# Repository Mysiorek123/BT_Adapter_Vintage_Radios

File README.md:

# Bluetooth Adapter for Vintage Radios

This project presents the design and implementation of a specialized Bluetooth adapter aimed at modernizing vintage radio receivers, such as the Polish Unitra Zodiak, while preserving their unique acoustic character. The hardware features a multi-stage power supply and signal isolation architecture, utilizing a bridge rectifier, high-capacity filtering, and a PS2561 optoisolator to eliminate hum and ground loops. 

# I/O Pinouts Description

- ~AC - AC Input Voltage (6,3V)
- J1 - Separated 1,2V DC Input
- J2 - Separated 1,2V Ground
- J3 - Bluetooth Power Supply (VCC)
- J4 - Bluetooth Ground (GND)

# Schematic Diagram

# PCB View

The physical implementation employs a double-sided PCB designed for a vertical "sandwich" stack configuration, ensuring full mechanical compatibility and efficient heat dissipation. 

# Components()
| Reference  | Footprint | Qty | Value / Description|
| :--- | :--- | :-: | :--- |
| **1** | J2 | SolderWire-0.1sqmm_1x01_D0.4mm_OD1mm | 1 | BT_VCC | |
| **2** | J1 | SolderWire-0.1sqmm_1x01_D0.4mm_OD1mm | 1 | 1V2_SEPARATED | |
| **3** | J3 | SolderWire-0.1sqmm_1x01_D0.4mm_OD1mm | 1 | BT_GND | |
| **4** | B1 | Diode_Bridge_19.0x3.5x10.0mm_P5.0mm | 1 | B40C2300-1500A | |
| **5** | C2, C4 | C_Axial_L3.8mm_D2.6mm_P7.50mm_Horizontal | 2 | 100nF | |
| **6** | U2 | TO-220-3_Vertical | 1 | LM7805 | |
| **7** | R2 | R_Axial_DIN0207_L6.3mm_D2.5mm_P7.62mm_Horizontal | 1 | 10k | |
| **8** | C3 | CP_Radial_D6.3mm_P2.50mm | 1 | 220uF | |
| **9** | I1 | SolderWire-0.1sqmm_1x02_P3.6mm_D0.4mm_OD1mm | 1 | AC | |
| **10** | R1 | R_Axial_DIN0207_L6.3mm_D2.5mm_P7.62mm_Horizontal | 1 | 220 | |
| **11** | Q1 | TO-220-3_Vertical | 1 | IRF620N | |
| **12** | C1 | CP_Radial_D10.0mm_P5.00mm | 1 | 2200uF | |
| **13** | U1 | DIP-4_W7.62mm | 1 | PS2561 | |

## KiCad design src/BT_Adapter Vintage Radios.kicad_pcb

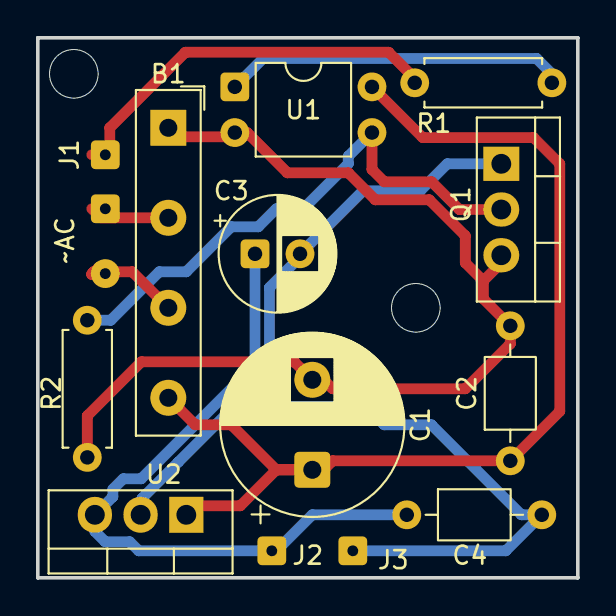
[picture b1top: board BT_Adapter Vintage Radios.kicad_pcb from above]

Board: 2 copper layers, 30.0 x 30.0 mm, 14 parts (0 on the bottom side), 9 nets.

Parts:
B1: B40C2300-1500A; Diode_Bridge_19.0x3.5x10.0mm_P5.0mm
C1: 2200uF; CP_Radial_D10.0mm_P5.00mm
C2, C4: 100nF; C_Axial_L3.8mm_D2.6mm_P7.50mm_Horizontal
C3: 220uF; CP_Radial_D6.3mm_P2.50mm
I1: AC; SolderWire-0.1sqmm_1x02_P3.6mm_D0.4mm_OD1mm
J1: 1V2_SEPARATED; SolderWire-0.1sqmm_1x01_D0.4mm_OD1mm
J2: BT_VCC; SolderWire-0.1sqmm_1x01_D0.4mm_OD1mm
J3: BT_GND; SolderWire-0.1sqmm_1x01_D0.4mm_OD1mm
Q1: IRF620N; TO-220-3_Vertical
R1: 220; R_Axial_DIN0207_L6.3mm_D2.5mm_P7.62mm_Horizontal
R2: 10k; R_Axial_DIN0207_L6.3mm_D2.5mm_P7.62mm_Horizontal
U1: PS2561; DIP-4_W7.62mm
U2: LM7805; TO-220-3_Vertical

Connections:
GND: B1.1 (-), C1.2, C2.2, Q1.3 (S), R2.2, U1.2
unnamed: B1.2, I1.1
unnamed: B1.3, I1.2
unnamed: J1.1, R1.1
unnamed: C3.1, C4.1, J2.1, U2.3 (VO)
unnamed: C3.2, C4.2, J3.1, Q1.1 (D), U2.2 (GND)
unnamed: Q1.2 (G), R2.1, U1.3
unnamed: R1.2, U1.1
VCC: B1.4 (+), C1.1, C2.1, U1.4, U2.1 (VI)

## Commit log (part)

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2026-05-10 Uploaded first circuit diagram and PCB layout
2026-05-10 Moved project files to src folder
2026-05-14 Minor improvements
